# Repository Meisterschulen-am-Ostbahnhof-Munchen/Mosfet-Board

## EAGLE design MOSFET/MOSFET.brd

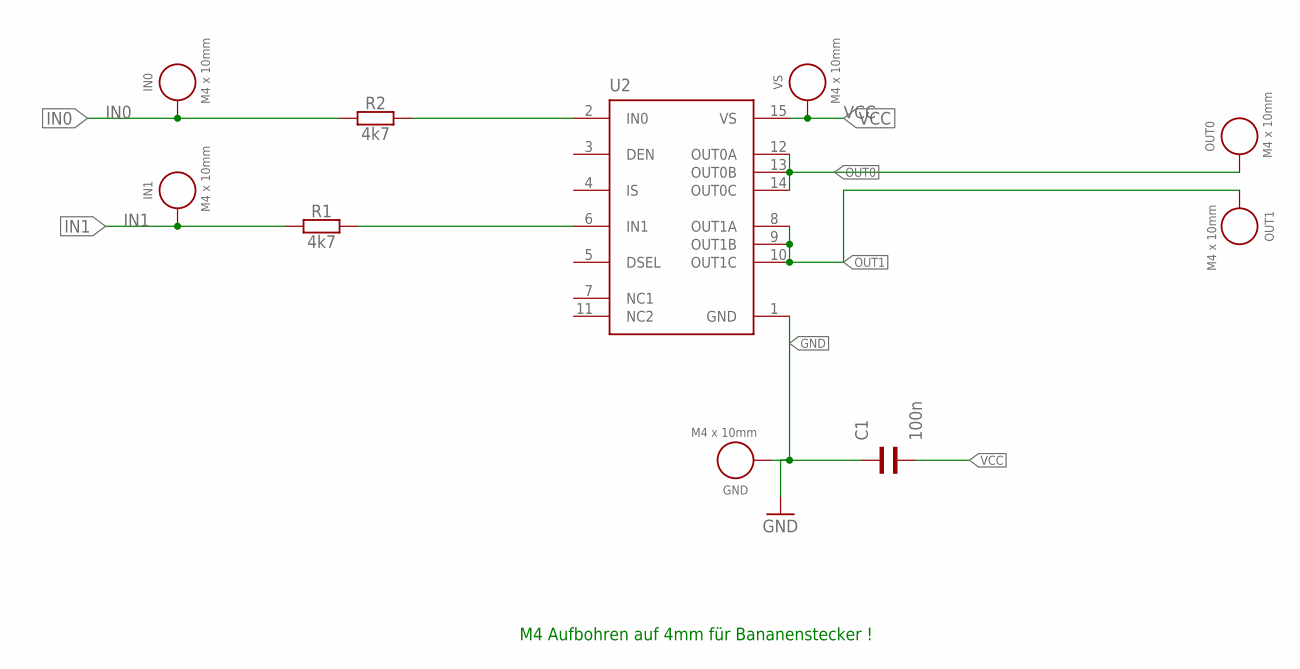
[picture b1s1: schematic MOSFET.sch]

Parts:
C1: 100n; WCAP-CSGP_0402
GND: M4 x 10mm; WA-SMSI_9774100482
IN0, IN1: M4 x 10mm; WA-SMSI_9774100482
OUT0, OUT1: M4 x 10mm; WA-SMSI_9774100482
R1, R2: 4k7; WCAP-CSRF_0402
U2: BTS7030-2EPA; SOP65P600X115-15N-V
VS: M4 x 10mm; WA-SMSI_9774100482

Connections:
GND: C1.2, GND.1, U2.1 (GND)
IN0: IN0.1, R2.1
IN1: IN1.1, R1.1
unnamed: R2.2, U2.2 (IN0)
unnamed: R1.2, U2.6 (IN1)
OUT0: OUT0.1, U2.12 (OUT0A), U2.13 (OUT0B), U2.14 (OUT0C)
OUT1: OUT1.1, U2.8 (OUT1A), U2.9 (OUT1B), U2.10 (OUT1C)
VCC: C1.1, U2.15 (VS), VS.1

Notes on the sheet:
M4 Aufbohren auf 4mm für Bananenstecker !

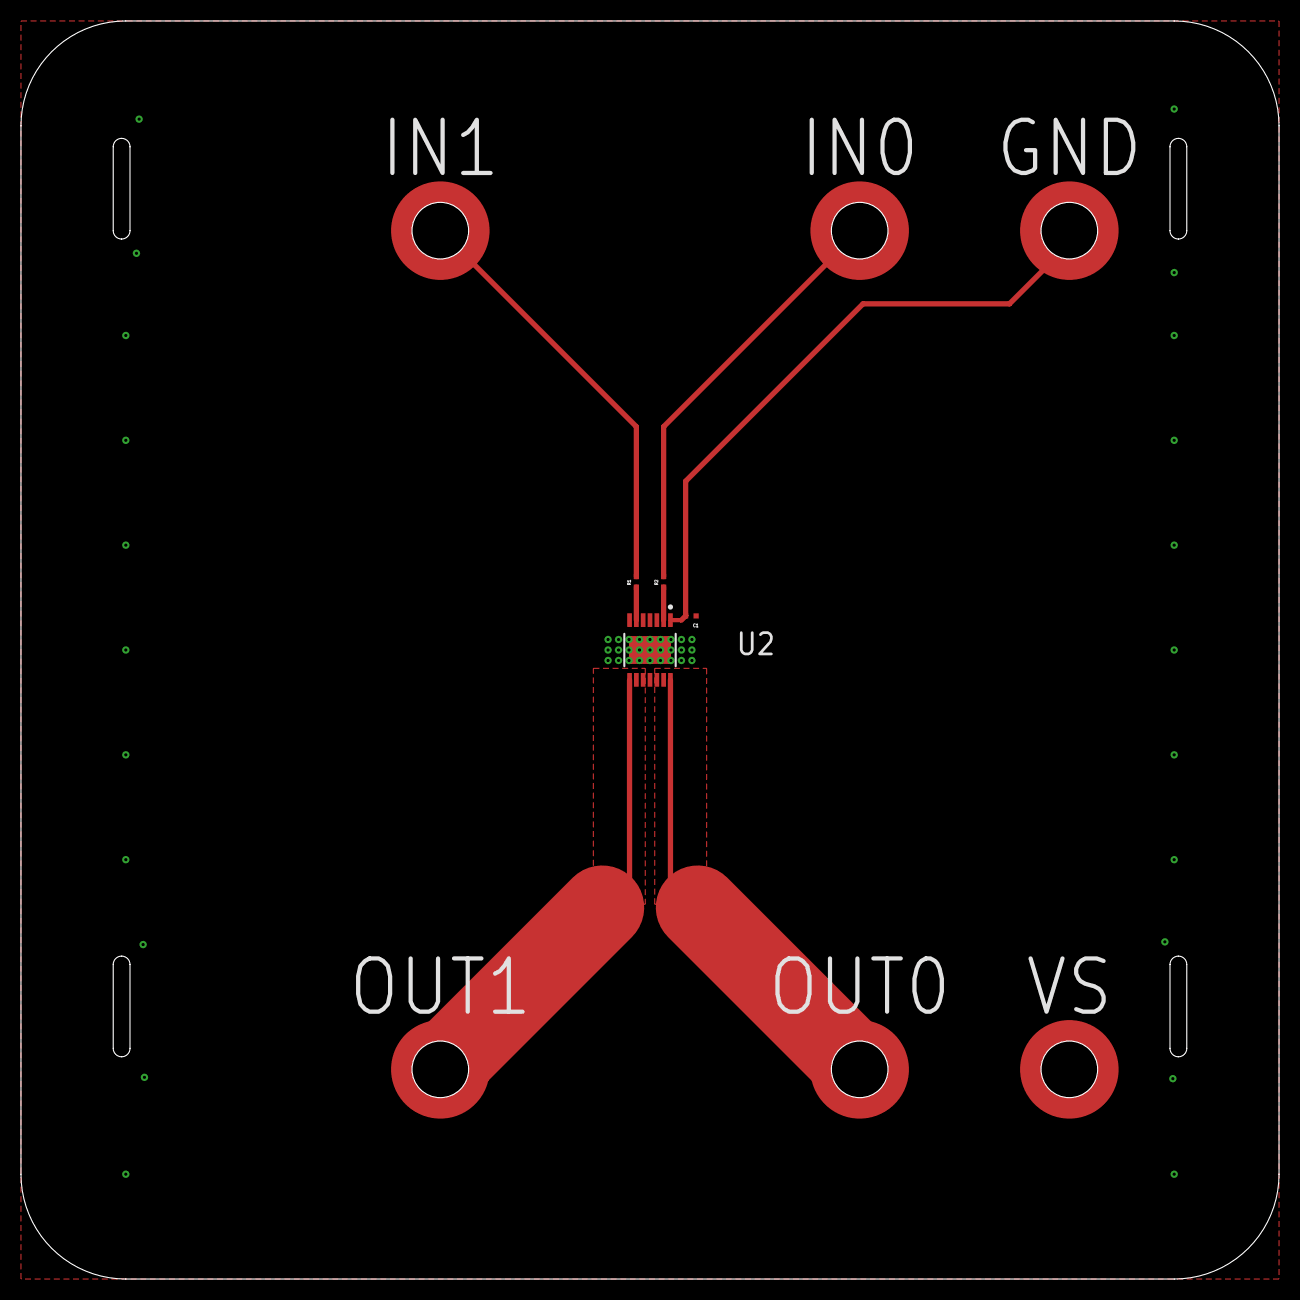
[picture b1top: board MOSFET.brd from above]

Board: 2 copper layers, 120.0 x 120.0 mm, 10 parts (0 on the bottom side), 8 nets.

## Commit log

2020-10-07 first
2020-10-07 Holder
2021-10-22 4mm Aufbohren !

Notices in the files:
parts and their libraries:
Wurth_Elektronik_Passive_Capacitors_rev1: Copyright: Würth Elektronik
